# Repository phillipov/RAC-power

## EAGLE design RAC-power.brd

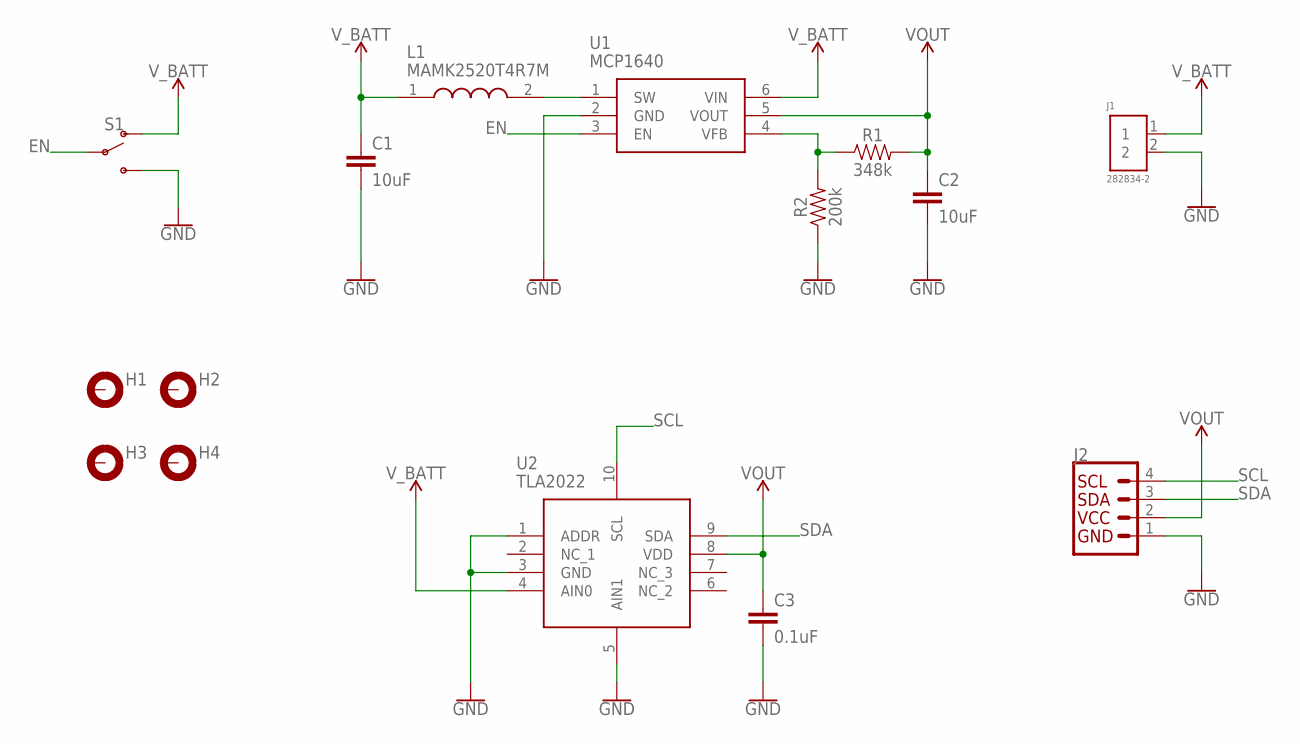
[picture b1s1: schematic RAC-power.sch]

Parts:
C1, C2: 10uF; 0603
C3: 0.1uF; 0603
H1, H2, H3, H4: MOUNT-PAD-ROUND2.8; 2,8-PAD
J1: 282834-2; CONN_282834-2
J2: QWIIC_CONNECTORJS-1MM; JST04_1MM_RA
L1: MAMK2520T4R7M; INDM2520X120N
R1: 348k; 0603
R2: 200k; 0603
S1: SWITCH-SPDT-SMD-AYZ0202; SWITCH_DPDT_SMD_AYZ0202
U1: MCP1640; SOT95P270X145-6N
U2: TLA2022; TLA2022IRUGR

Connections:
EN: S1.2, U1.3 (EN)
GND: C1.2, C2.2, C3.2, J1.2, J2.1, R2.1, S1.3 (S), U1.2 (GND), U2.1 (ADDR), U2.3 (GND), U2.5 (AIN1)
SCL: J2.4, U2.10 (SCL)
SDA: J2.3, U2.9 (SDA)
SW: L1.2, U1.1 (SW)
VFB: R1.1, R2.2, U1.4 (VFB)
VOUT: C2.1, C3.1, J2.2, R1.2, U1.5 (VOUT), U2.8 (VDD)
V_BATT: C1.1, J1.1, L1.1, S1.1 (O), U1.6 (VIN), U2.4 (AIN0)

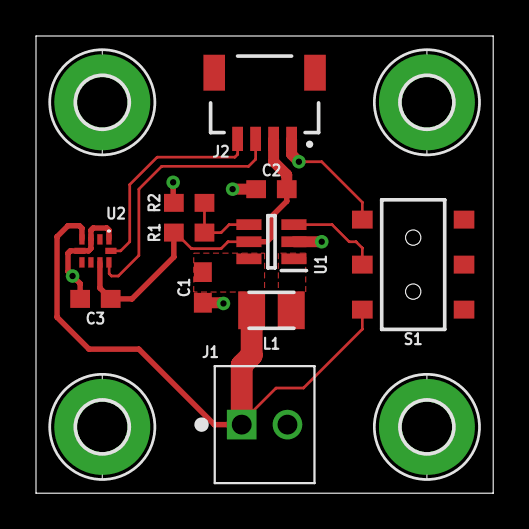
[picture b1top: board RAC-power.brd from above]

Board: 2 copper layers, 25.4 x 25.4 mm, 15 parts (0 on the bottom side), 8 nets.

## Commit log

2019-08-18 Created a basic MCP1640 boost schematic
2019-08-19 Added battery monitor ADC, JST connector, and mounting holes
2019-08-19 Laid out components and named some nets
2019-08-19 Fully routed board and cleared DRC

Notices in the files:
parts and their libraries:
SparkFun-Capacitors: Licensing: Creative Commons ShareAlike 4.0 International - https://creativecommons.org/licenses/by-sa/4.0
